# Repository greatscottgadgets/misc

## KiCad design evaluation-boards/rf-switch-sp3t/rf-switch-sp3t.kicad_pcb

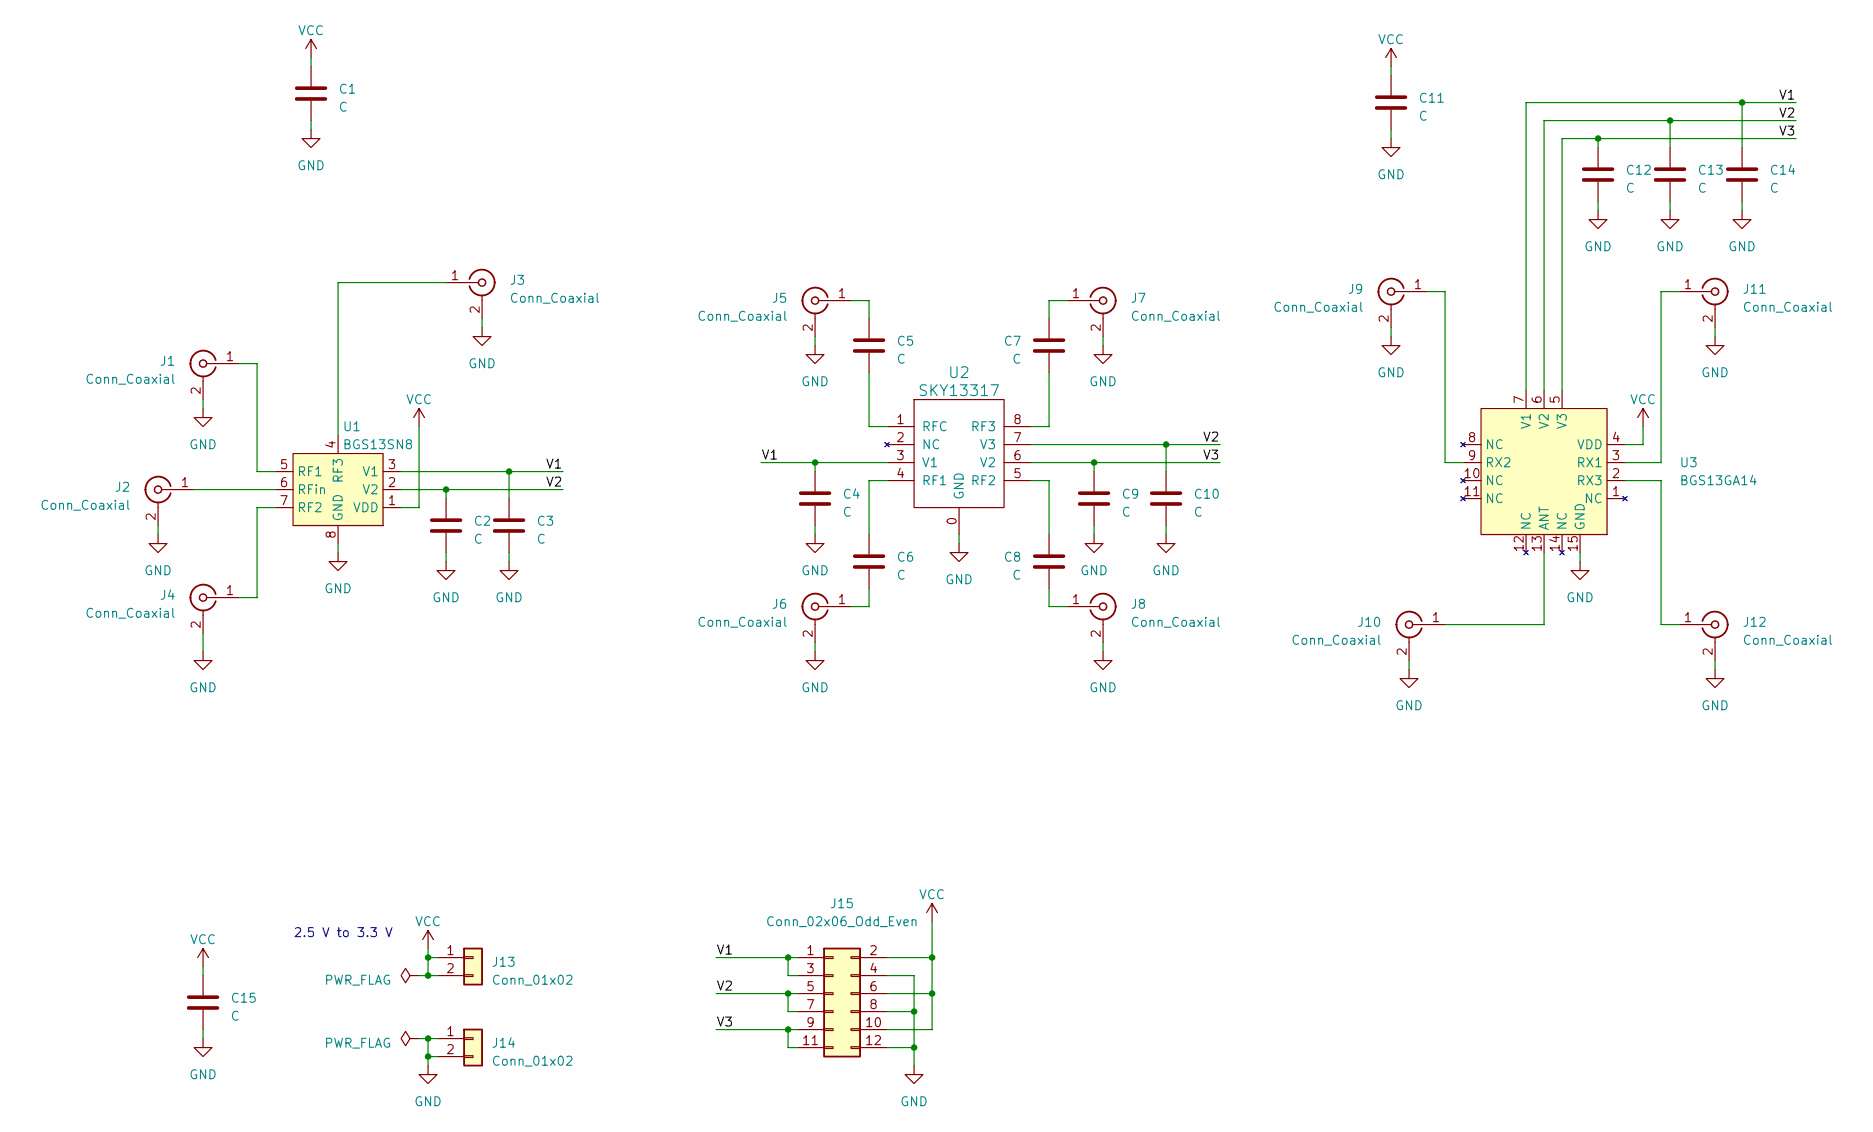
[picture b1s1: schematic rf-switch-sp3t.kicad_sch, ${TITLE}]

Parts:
C1, C2, C3, C4, C5, C6, C7, C8, C9, C10, C11, C12, C13, C14, C15: C; C_0201_0603Metric
J1, J2, J3, J4, J5, J6, J7, J8, J9, J10, J11, J12: Conn_Coaxial; Linx_SMA_CONSMA003.062
J13, J14: Conn_01x02; PinHeader_1x02_P2.54mm_Vertical
J15: Conn_02x06_Odd_Even; PinHeader_2x06_P2.54mm_Vertical
U1: BGS13SN8; TSNP-9-3
U2: SKY13317; SKY13317-373LF
U3: BGS13GA14; ATSLP-14-1EP_2x2mm_P0.4mm_EP1x1mm

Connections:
/V1: C3.1, C4.1, C14.1, J15.1, J15.3, U1.3 (V1), U2.3 (V1), U3.7 (V1)
/V2: C2.1, C10.1, C13.1, J15.5, J15.7, U1.2 (V2), U2.7 (V3), U3.6 (V2)
/V3: C9.1, C12.1, J15.9, J15.11, U2.6 (V2), U3.5 (V3)
GND: C1.2, C2.2, C3.2, C4.2, C9.2, C10.2, C11.2, C12.2, C13.2, C14.2, C15.2, J1.2 (Ext), J2.2 (Ext), J3.2 (Ext), J4.2 (Ext), J5.2 (Ext), J6.2 (Ext), J7.2 (Ext), J8.2 (Ext), J9.2 (Ext), J10.2 (Ext), J11.2 (Ext), J12.2 (Ext), J14.1, J14.2, J15.4, J15.8, J15.12, U1.8 (GND), U1.9 (GND), U2.0 (GND), U3.15 (GND)
unnamed: J1.1 (In), U1.5 (RF1)
unnamed: J2.1 (In), U1.6 (RFin)
unnamed: J3.1 (In), U1.4 (RF3)
unnamed: J4.1 (In), U1.7 (RF2)
unnamed: C5.1, J5.1 (In)
unnamed: C6.2, J6.1 (In)
unnamed: C7.1, J7.1 (In)
unnamed: C8.2, J8.1 (In)
unnamed: J9.1 (In), U3.9 (RX2)
unnamed: J10.1 (In), U3.13 (ANT)
unnamed: J11.1 (In), U3.3 (RX1)
unnamed: J12.1 (In), U3.2 (RX3)
unnamed: C6.1, U2.4 (RF1)
unnamed: C8.1, U2.5 (RF2)
unnamed: C7.2, U2.8 (RF3)
unnamed: C5.2, U2.1 (RFC)
VCC: C1.1, C11.1, C15.1, J13.1, J13.2, J15.2, J15.6, J15.10, U1.1 (VDD), U3.4 (VDD)

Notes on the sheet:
2.5 V to 3.3 V

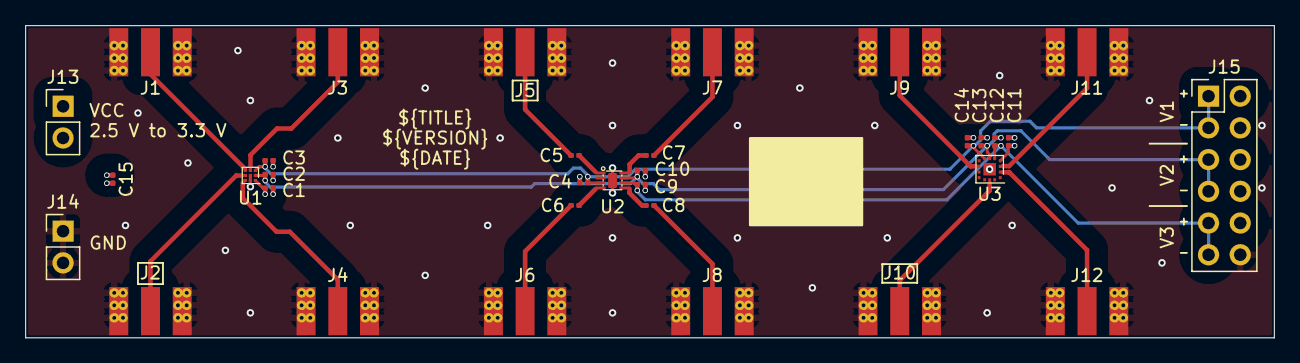
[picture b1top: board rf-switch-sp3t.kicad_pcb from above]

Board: 4 copper layers, 100.0 x 25.0 mm, 33 parts (0 on the bottom side), 21 nets.

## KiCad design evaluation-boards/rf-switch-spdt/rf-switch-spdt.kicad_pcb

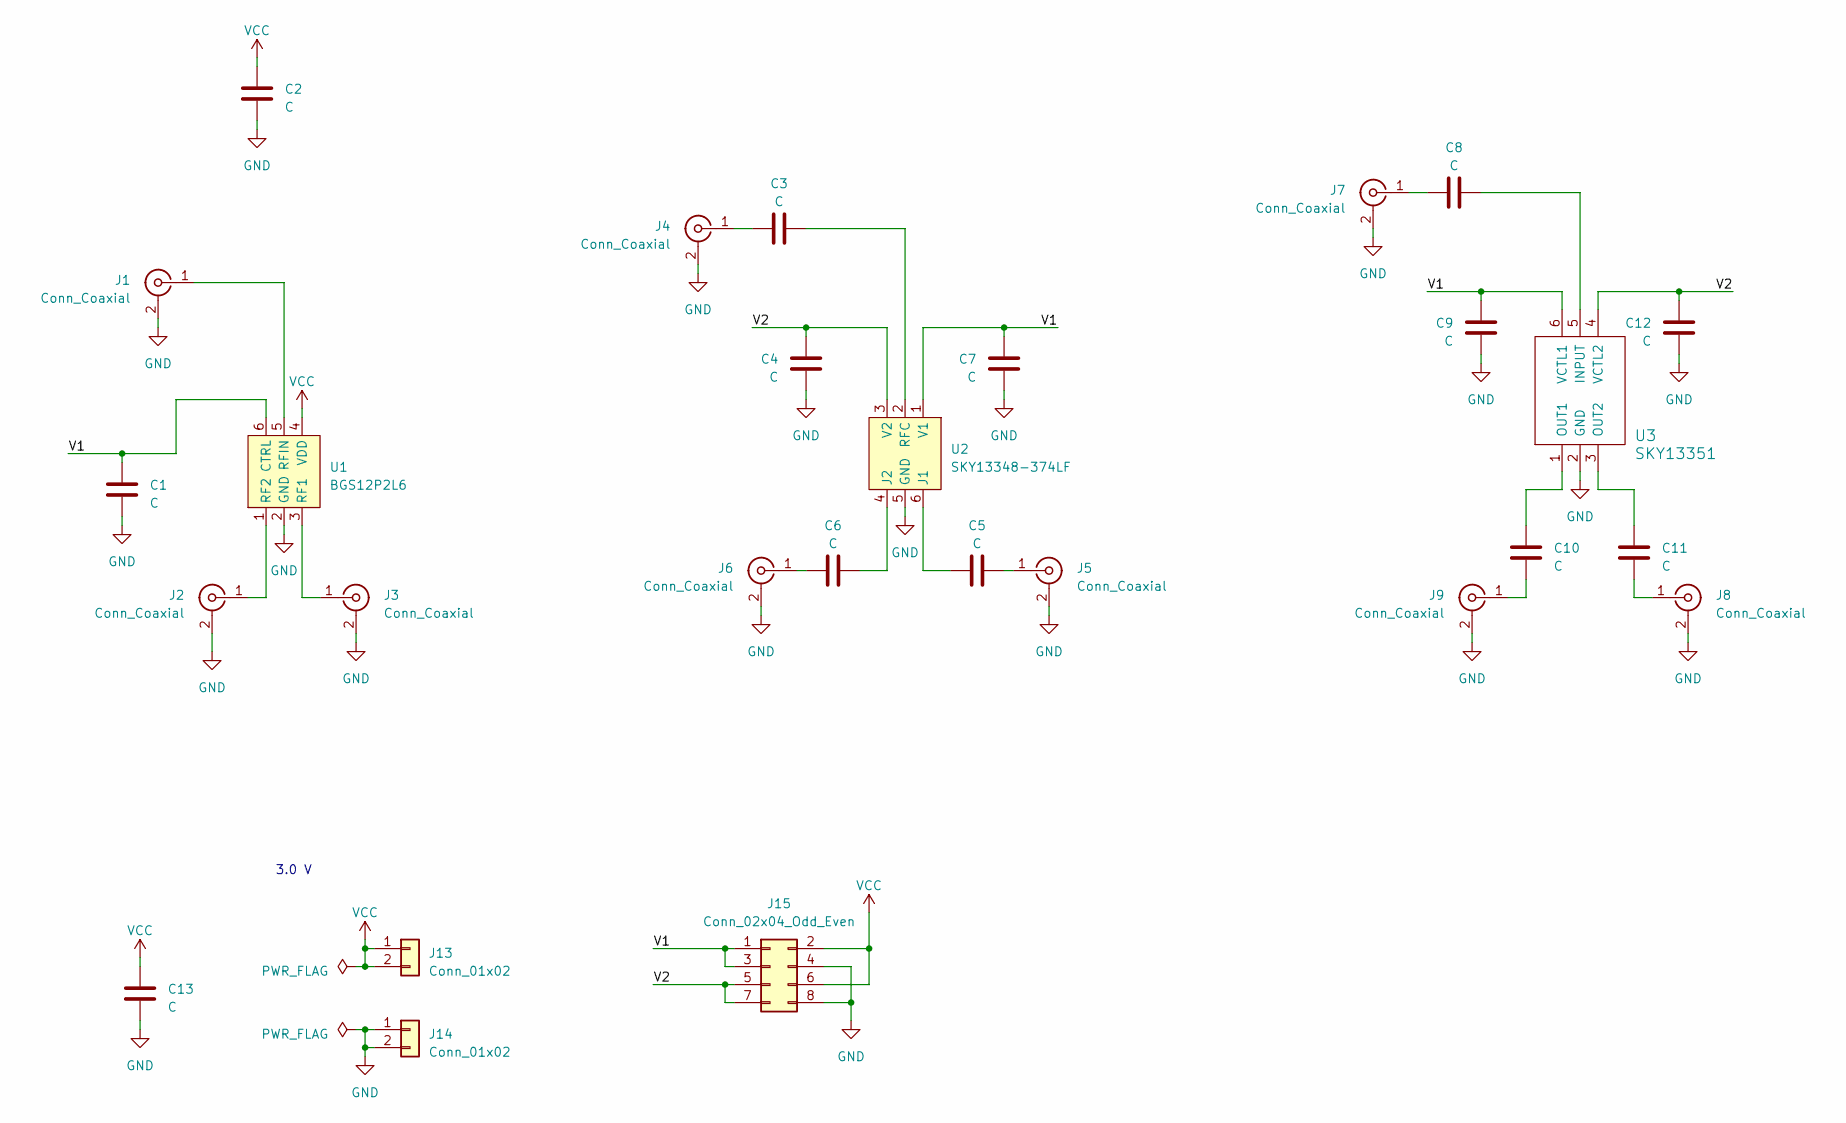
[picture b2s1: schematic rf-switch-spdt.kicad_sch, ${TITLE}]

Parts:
C1, C2, C3, C4, C5, C6, C7, C8, C9, C10, C11, C12, C13: C; C_0201_0603Metric
J1, J2, J3, J4, J5, J6, J7, J8, J9: Conn_Coaxial; Linx_SMA_CONSMA003.062
J13, J14: Conn_01x02; PinHeader_1x02_P2.54mm_Vertical
J15: Conn_02x04_Odd_Even; PinHeader_2x04_P2.54mm_Vertical
U1: BGS12P2L6; TSLP-6-4_1.1x0.7mm_P0.4mm
U2: SKY13348-374LF; Skyworks_SKY65404-31
U3: SKY13351; SKY13351-378LF

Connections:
/V1: C1.1, C7.1, C9.1, J15.1, J15.3, U1.6 (CTRL), U2.1 (V1), U3.6 (VCTL1)
/V2: C4.1, C12.1, J15.5, J15.7, U2.3 (V2), U3.4 (VCTL2)
GND: C1.2, C2.2, C4.2, C7.2, C9.2, C12.2, C13.2, J1.2 (Ext), J2.2 (Ext), J3.2 (Ext), J4.2 (Ext), J5.2 (Ext), J6.2 (Ext), J7.2 (Ext), J8.2 (Ext), J9.2 (Ext), J14.1, J14.2, J15.4, J15.8, U1.2 (GND), U2.5 (GND), U2.7 (GND), U3.2 (GND)
unnamed: J1.1 (In), U1.5 (RFIN)
unnamed: J2.1 (In), U1.1 (RF2)
unnamed: J3.1 (In), U1.3 (RF1)
unnamed: C3.1, J4.1 (In)
unnamed: C5.2, J5.1 (In)
unnamed: C6.1, J6.1 (In)
unnamed: C8.1, J7.1 (In)
unnamed: C11.2, J8.1 (In)
unnamed: C10.2, J9.1 (In)
unnamed: C5.1, U2.6 (J1)
unnamed: C6.2, U2.4 (J2)
unnamed: C3.2, U2.2 (RFC)
unnamed: C8.2, U3.5 (INPUT)
unnamed: C10.1, U3.1 (OUT1)
unnamed: C11.1, U3.3 (OUT2)
VCC: C2.1, C13.1, J13.1, J13.2, J15.2, J15.6, U1.4 (VDD)

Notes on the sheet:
3.0 V

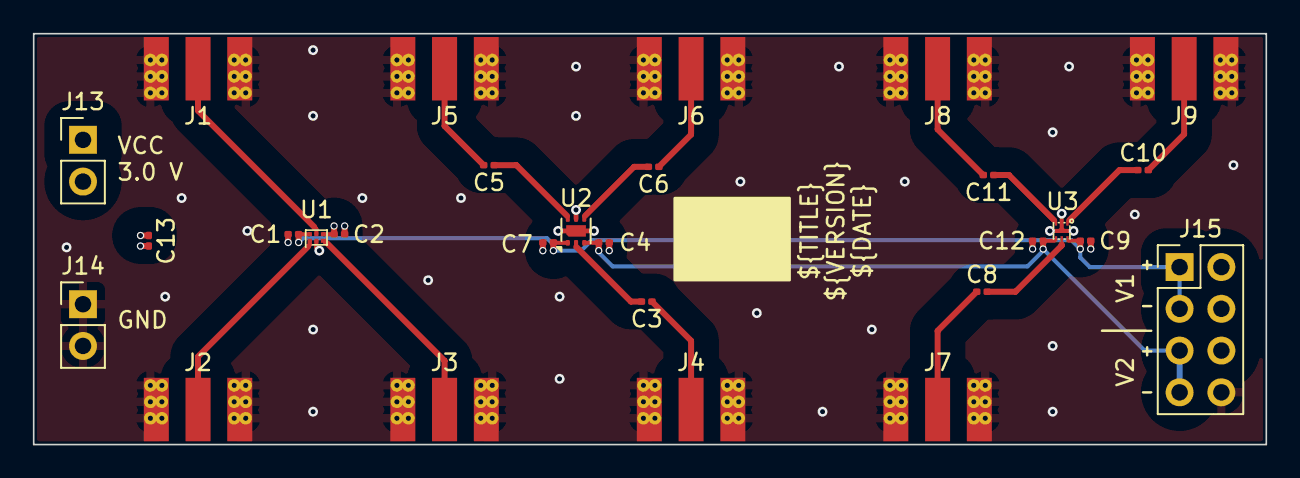
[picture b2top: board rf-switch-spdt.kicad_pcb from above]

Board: 4 copper layers, 75.0 x 25.0 mm, 28 parts (0 on the bottom side), 19 nets.

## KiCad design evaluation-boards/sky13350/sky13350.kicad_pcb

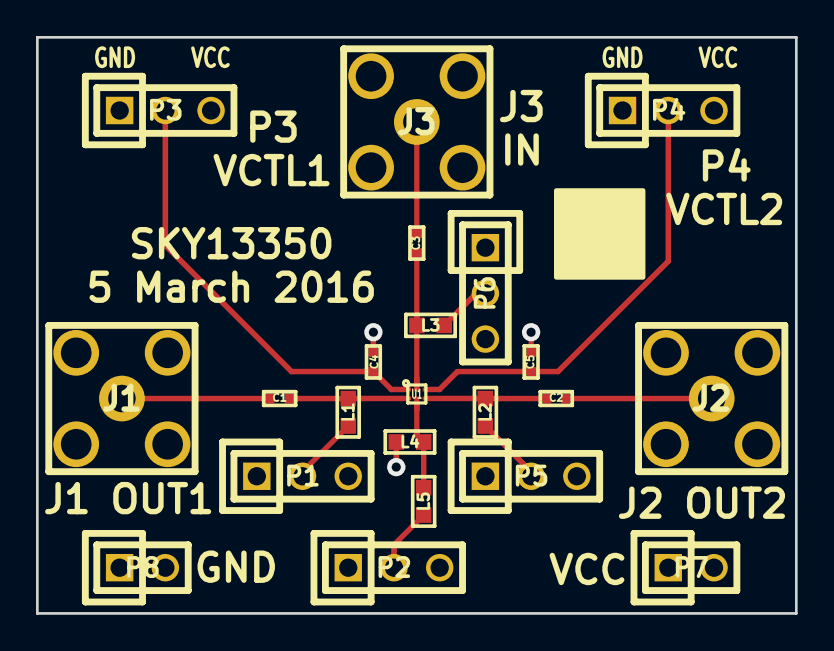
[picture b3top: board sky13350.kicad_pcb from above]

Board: 4 copper layers, 42.2 x 32.0 mm, 22 parts (0 on the bottom side), 15 nets.

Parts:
C1, C2, C3: 100nF; 0402
C4, C5: 33pF; 0402
J1, J2, J3: SMA; SMA-VERTICAL
L1, L2, L3, L4, L5: 15uH; 0603
P1, P2, P3, P4, P5, P6: CONN_01X03; HEADER-1x3
P7, P8: CONN_01X02; HEADER-1x2
U1: SKY13350; SKY13350-385LF

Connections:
GND: C4.2, C5.1, J1.2, J2.2, J3.2, L4.1, P1.1, P2.1, P3.1, P4.1, P5.1, P6.1, P8.1, P8.2
unnamed: C1.1, L1.2, U1.2
unnamed: C1.2, J1.1
unnamed: C2.1, J2.1
unnamed: C2.2, L2.2, U1.4
unnamed: C3.1, J3.1
unnamed: C3.2, L3.2, U1.6
unnamed: C4.1, P3.2, U1.1
unnamed: C5.2, P4.2, U1.5
unnamed: L1.1, P1.2
unnamed: L2.1, P5.2
unnamed: L3.1, P6.2
unnamed: L4.2, L5.2, U1.3
unnamed: L5.1, P2.2
VCC: P1.3, P2.3, P3.3, P4.3, P5.3, P6.3, P7.1, P7.2

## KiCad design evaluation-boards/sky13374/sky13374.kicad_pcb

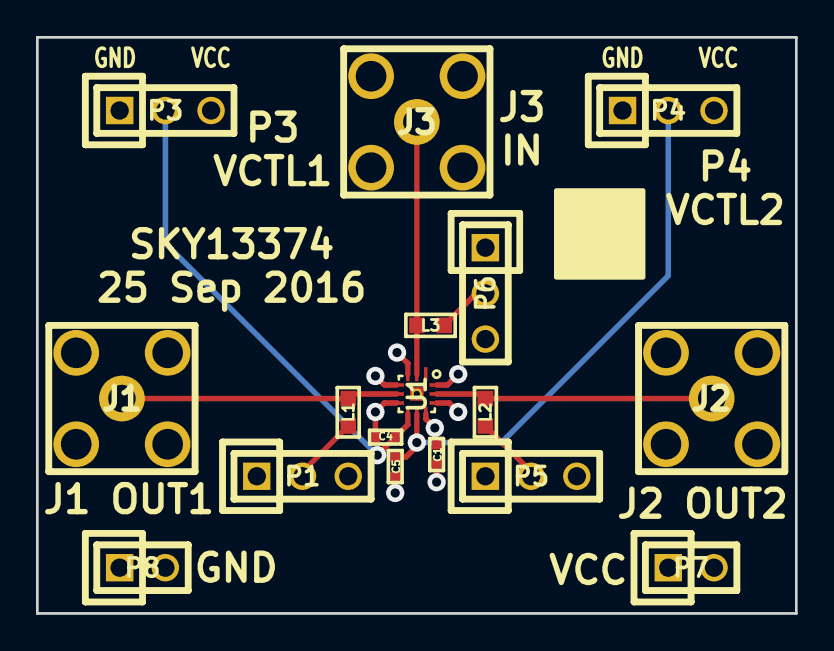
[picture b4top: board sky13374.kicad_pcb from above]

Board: 4 copper layers, 42.2 x 32.0 mm, 17 parts (0 on the bottom side), 10 nets.

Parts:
C1: 100nF; 0402
C4, C5: 33pF; 0402
J1, J2, J3: SMA; SMA-VERTICAL
L1, L2, L3: 15uH; 0603
P1, P3, P4, P5, P6: CONN_01X03; HEADER-1x3
P7, P8: CONN_01X02; HEADER-1x2
U1: SKY13374; SKY13374-397LF

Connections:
GND: C1.1, C4.2, C5.1, J1.2, J2.2, J3.2, P1.1, P3.1, P4.1, P5.1, P6.1, P8.1, P8.2, U1.0, U1.3, U1.4, U1.6, U1.10, U1.12
unnamed: C4.1, P3.2, U1.7
unnamed: C5.2, P4.2, U1.8
unnamed: J1.1, L1.2, U1.5
unnamed: J2.1, L2.2, U1.11
unnamed: J3.1, L3.2, U1.2
unnamed: L1.1, P1.2
unnamed: L2.1, P5.2
unnamed: L3.1, P6.2
VCC: C1.2, P1.3, P3.3, P4.3, P5.3, P6.3, P7.1, P7.2, U1.9

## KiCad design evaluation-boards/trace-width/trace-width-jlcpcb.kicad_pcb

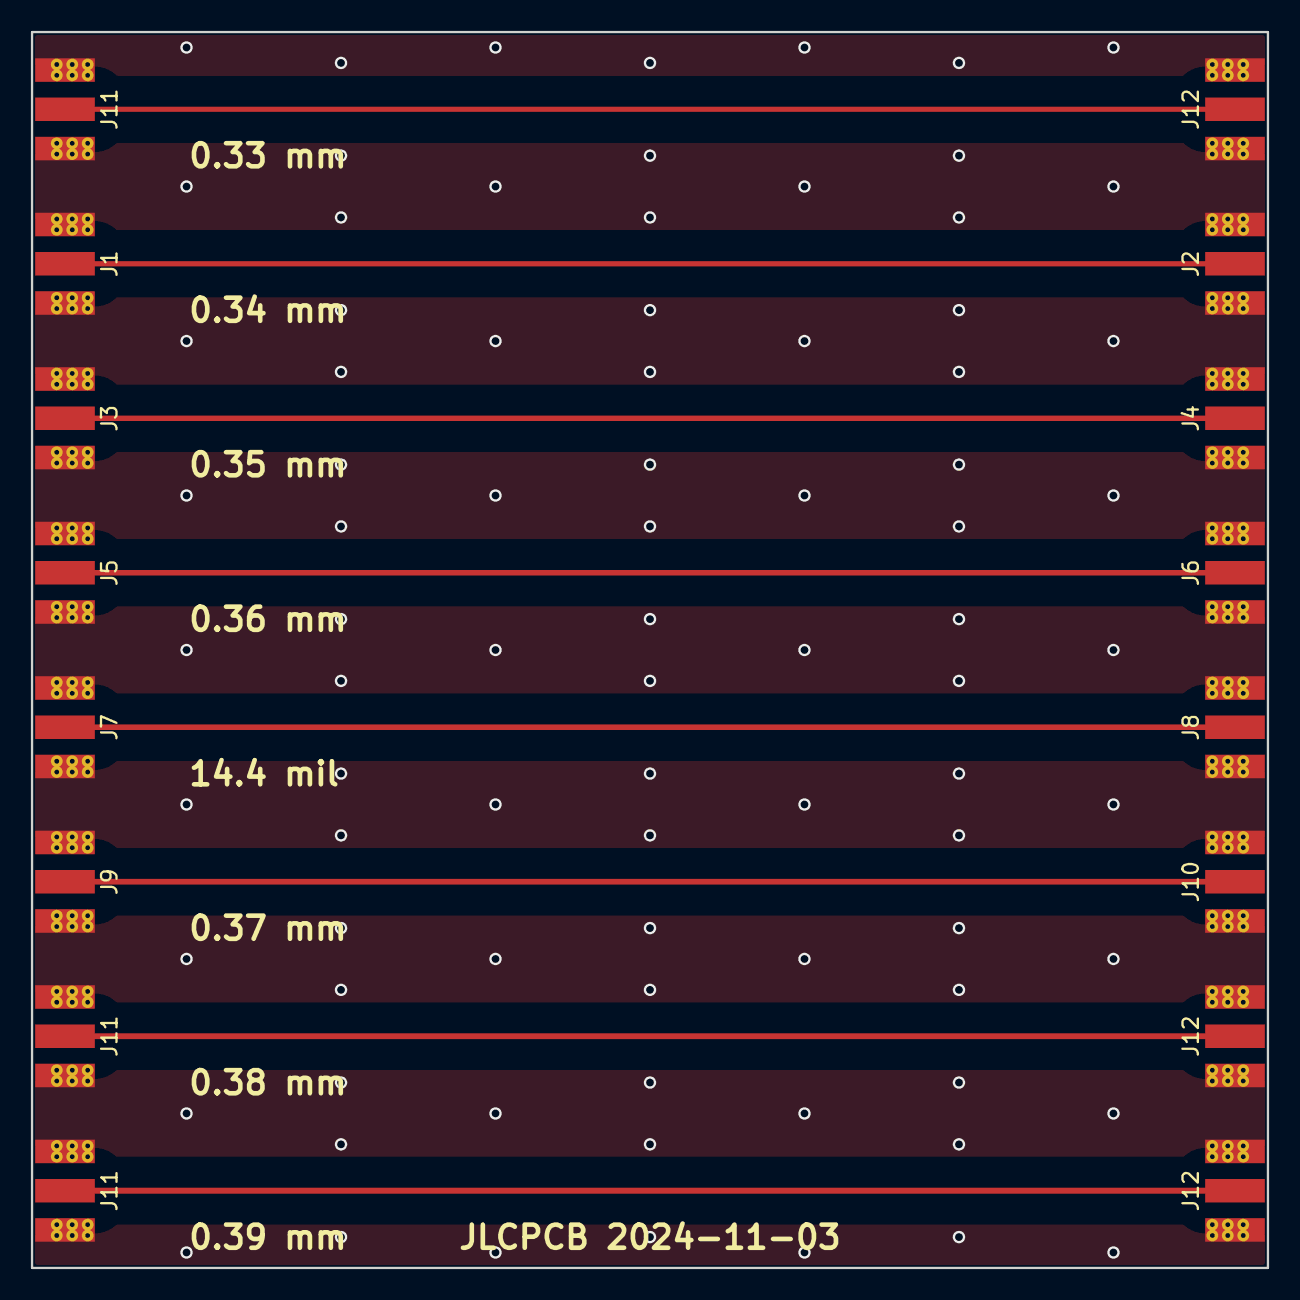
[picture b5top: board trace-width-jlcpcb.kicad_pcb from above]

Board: 6 copper layers, 80.0 x 80.0 mm, 16 parts (0 on the bottom side), 7 nets.

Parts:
J1, J2, J3, J4, J5, J6, J7, J8, J9, J10, J11, J11#2, J11#3, J12, J12#2, J12#3: CONN_COAXIAL; Linx_SMA_CONSMA003.062

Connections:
GND: J1.2, J2.2, J3.2, J4.2, J5.2, J6.2, J7.2, J8.2, J9.2, J10.2, J11.2, J11#2.2, J11#3.2, J12.2, J12#2.2, J12#3.2
unnamed: J1.1, J2.1
unnamed: J3.1, J4.1
unnamed: J5.1, J6.1
unnamed: J7.1, J8.1
unnamed: J9.1, J10.1
unnamed: J11.1, J11#2.1, J11#3.1, J12.1, J12#2.1, J12#3.1

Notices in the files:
parts and their libraries:
COPYRIGHT: Copyright 2023-2024 Great Scott Gadgets
LICENSE: Licensed under the CERN-OHL-P v2
